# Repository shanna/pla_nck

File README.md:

# PLA_NCK

A low profile split keyboard I built using Gateron KS-33 low profile switches.

## Story

I had assembled a Ferris Sweep previously but I hated the Kailh Low Profile Choc Switches but but wanted something low profile.
Sincve I couldn't find anything at the time I decided to learn KiCad and Fusion360 to create my own design.

I've called it the PLA_NCK because my original intention was to create a split [ZSA Planck EZ](https://blog.zsa.io/2307-goodbye-planck-ez/) (discontinued) since it has probably been my favourite layout to date. I justed wanted a split, bluetooth and low profile version with Gateron KS-33 switches after using the [NuPhy Air60](https://nuphy.com/collections/keyboards/products/air60) with [Daisy](https://nuphy.com/collections/switches/products/nuphy-daisy-l48-switches) Gateron colaboration switches.
I couldn't quite fit the controller under the keys while keeping it low so I gave up and added the nice view as well for this version so my homage to the original Planck is a bit shit. 
I might attempt it again with without a pre-made controller when my KiCad skills improve so I can ditch the display and make it closer to the split plank low profile vision I started with.

## BOM

The AliExpress stuff will be hit and miss.

* NuPhy [Daisy](https://nuphy.com/collections/switches/products/nuphy-daisy-l48-switches) switches.
* NuPhy [COAST Twilight nSA Dye-sub PBT Keycaps](https://nuphy.com/collections/keycaps/products/twilight-nsa-dye-sub-pbt-keycaps)
* GATERON KS-27 or KS-33 [Low Profile switch Hot-swap PCB 2.0 Socket](https://www.aliexpress.com/item/1005004128409069.html) these were hard to find.
* PCB and Plate [JLCPCB](https://jlcpcb.com) was much cheaper than PCBWay when I got a quote for the exported gerbers. The quaility was fine.
* 4xM2 4mm screws.
* 8xM2 12-14mm screws.
* 12 x [M2 OD3.5mm 3mm](https://www.aliexpress.com/item/1005003582355741.html) brass hot melt insert nuts.
* 3D printer for the case, cover and optional nice view guard.

## Build

Everything you need is included in this repo I think.

1. You need to order both the plate and PCB as the GATERON KS-33 keys are only 3 pin and don't have the plastic alignment tabs so can only be used hot-swap with this design.
2. The nice view guard is in case you are worried about shorting your nice view on the battery case material.
3. I 3D printed the cover without a top and bottom layer using 60% infilled 3D honeycomb pattern. I paused the print at layer 78 to change my matte black PLA out for matte grey. I've included the bambu studio files if you happen to own a Bambu Labs printer or can use the configuration.

### CAD - V1 3D Printed Case 

Version 1 I tried to add mass by printing the case with 60% infill in PLA and hoped it would improve the sound. It was better than nothing but a bit too loud for the office.

### CAD - V2 3D Printed Case

Version 2 I've simplified the PLA case and printed a mount in TPU that sits between the PCB and plate and bolts directly to the case. Keyboard switch sounds is subjective (some blue use MX blues) but this removed a lot of the high frequency plastic "ping" I wasn't happy with. There is still room for improvement if you have any ideas. I've been experimenting with different foams and TPU inserts in the case to remove more of the high frequencies because I want more "thock" and less "clack".

## Firmware

I'm running ZMK on my nice!nano's. The config/ directory contains all the ZMK config you need to match the pin-out and diode direction along with my current key map (which sucks but is a starting point).

The makefile expects nix to be installed and runs 'act' the local github actions runner to test the ZMK github actions. It has nowhere to write artifacts out to but is handy for checking your configuration files are valid before uploading them to github.

## Issues

Tolerances are tight, too tight in places, depending on the PCB manufacturer and 3D printer setup and material you print in. I used PLA but I still struggled with shrinkage so tried to hide it with some shadow lines.

* The switch footprint is slightly too tight and can locks on to the switch housing making it hard to hot-swap switches.
* The plate was a tight fit, again making the switches hard to hot-swap.
* My attempt at an injection molding style shadow lines could be improved. They just look like gaps between the PCB and case because I made them so deep.
* It would be cool if the USB and power switch gap was more exact and the PCB lined up with the side of the 3D printed case a bit better.

## Gallery

### V1

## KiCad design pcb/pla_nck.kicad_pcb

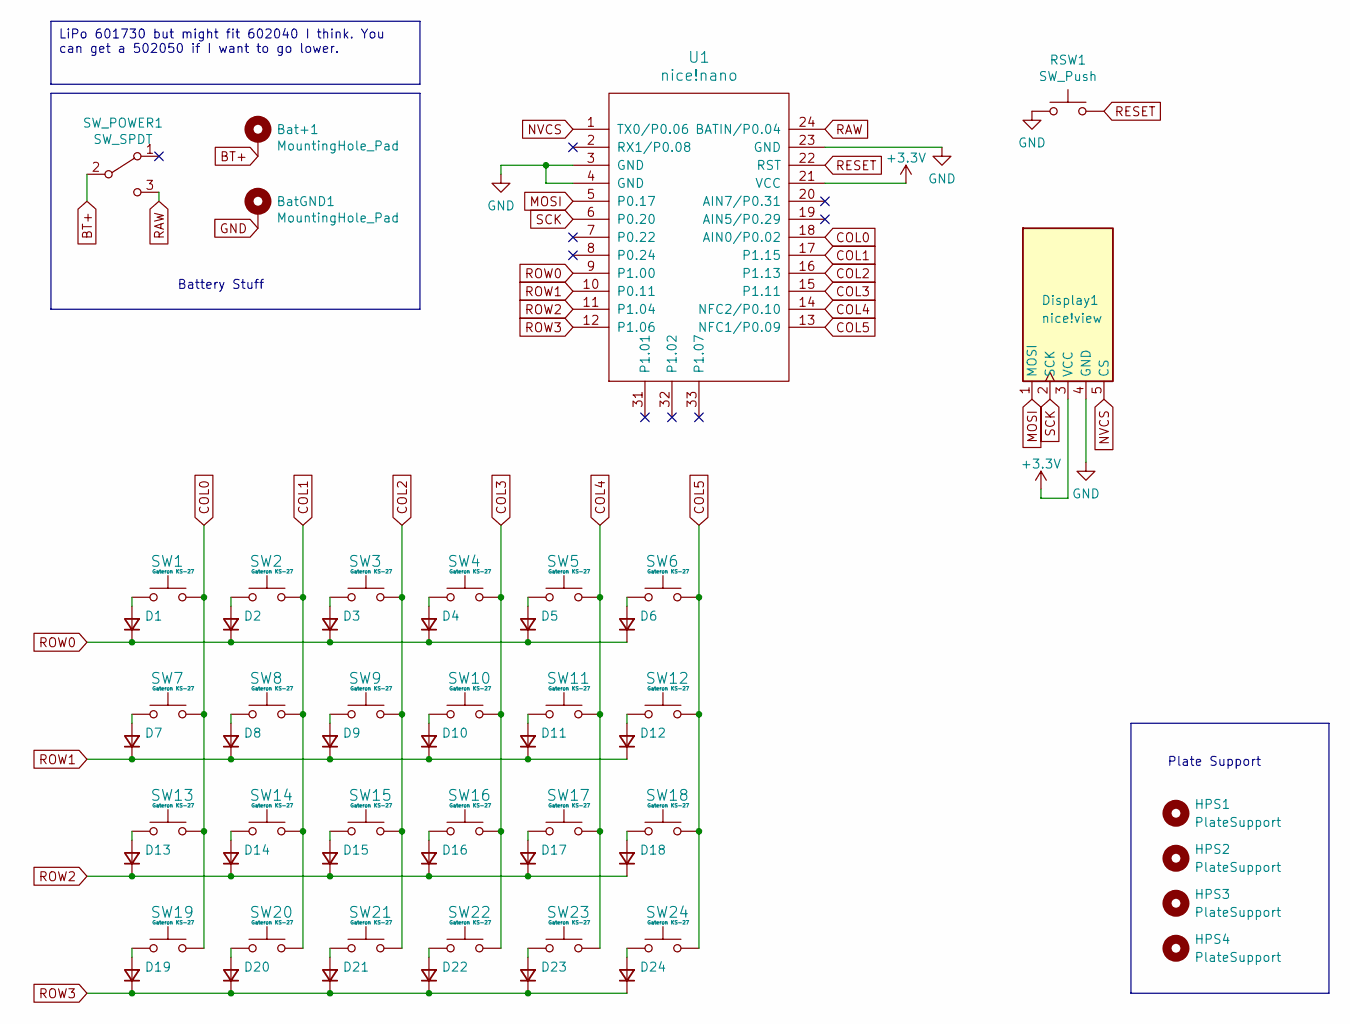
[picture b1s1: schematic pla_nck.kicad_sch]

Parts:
Bat+1: MountingHole_Pad; 1pin_battery_v2
BatGND1: MountingHole_Pad; 1pin_battery_v2
D1, D2, D3, D4, D5, D6, D7, D8, D9, D10, D11, D12, D13, D14, D15, D16, D17, D18, D19, D20, D21, D22, D23, D24: diode; D_SOD-123
Display1: nice!view; nice_view
HPS1, HPS2, HPS3, HPS4: PlateSupport; MountingHole_2.2mm_M2
RSW1: SW_Push; SW_RESET
SW1, SW2, SW3, SW4, SW5, SW6, SW7, SW8, SW9, SW10, SW11, SW12, SW13, SW14, SW15, SW16, SW17, SW18, SW19, SW20, SW21, SW22, SW23, SW24: Gateron KS-27; SW_Gateron_LO_PRO_1.00u_HOTSWAP_NO_LED_PCB
SW_POWER1: SW_SPDT; smt-slider-switch
U1: nice!nano; nice_nano

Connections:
+3V3: Display1.3 (VCC), U1.21 (VCC)
BT+: Bat+1.1, SW_POWER1.2 (B)
COL0: SW1.2, SW7.2, SW13.2, SW19.2, U1.18 (AIN0/P0.02)
COL1: SW2.2, SW8.2, SW14.2, SW20.2, U1.17 (P1.15)
COL2: SW3.2, SW9.2, SW15.2, SW21.2, U1.16 (P1.13)
COL3: SW4.2, SW10.2, SW16.2, SW22.2, U1.15 (P1.11)
COL4: SW5.2, SW11.2, SW17.2, SW23.2, U1.14 (NFC2/P0.10)
COL5: SW6.2, SW12.2, SW18.2, SW24.2, U1.13 (NFC1/P0.09)
GND: BatGND1.1, Display1.4 (GND), RSW1.1, U1.3 (GND), U1.4 (GND), U1.23 (GND)
MOSI: Display1.1 (MOSI), U1.5 (P0.17)
NVCS: Display1.5 (CS), U1.1 (TX0/P0.06)
unnamed: D1.2 (A), SW1.1
unnamed: D2.2 (A), SW2.1
unnamed: D3.2 (A), SW3.1
unnamed: D4.2 (A), SW4.1
unnamed: D5.2 (A), SW5.1
unnamed: D6.2 (A), SW6.1
unnamed: D7.2 (A), SW7.1
unnamed: D8.2 (A), SW8.1
unnamed: D9.2 (A), SW9.1
unnamed: D10.2 (A), SW10.1
unnamed: D11.2 (A), SW11.1
unnamed: D12.2 (A), SW12.1
unnamed: D13.2 (A), SW13.1
unnamed: D14.2 (A), SW14.1
unnamed: D15.2 (A), SW15.1
unnamed: D16.2 (A), SW16.1
unnamed: D17.2 (A), SW17.1
unnamed: D18.2 (A), SW18.1
unnamed: D19.2 (A), SW19.1
unnamed: D20.2 (A), SW20.1
unnamed: D21.2 (A), SW21.1
unnamed: D22.2 (A), SW22.1
unnamed: D23.2 (A), SW23.1
unnamed: D24.2 (A), SW24.1
RAW: SW_POWER1.3 (C), U1.24 (BATIN/P0.04)
RESET: RSW1.2, U1.22 (RST)
ROW0: D1.1 (K), D2.1 (K), D3.1 (K), D4.1 (K), D5.1 (K), D6.1 (K), U1.9 (P1.00)
ROW1: D7.1 (K), D8.1 (K), D9.1 (K), D10.1 (K), D11.1 (K), D12.1 (K), U1.10 (P0.11)
ROW2: D13.1 (K), D14.1 (K), D15.1 (K), D16.1 (K), D17.1 (K), D18.1 (K), U1.11 (P1.04)
ROW3: D19.1 (K), D20.1 (K), D21.1 (K), D22.1 (K), D23.1 (K), D24.1 (K), U1.12 (P1.06)
SCK: Display1.2 (SCK), U1.6 (P0.20)

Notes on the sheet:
LiPo 601730 but might fit 602040 I think. You can get a 502050 if I want to go lower.
Battery Stuff
Plate Support

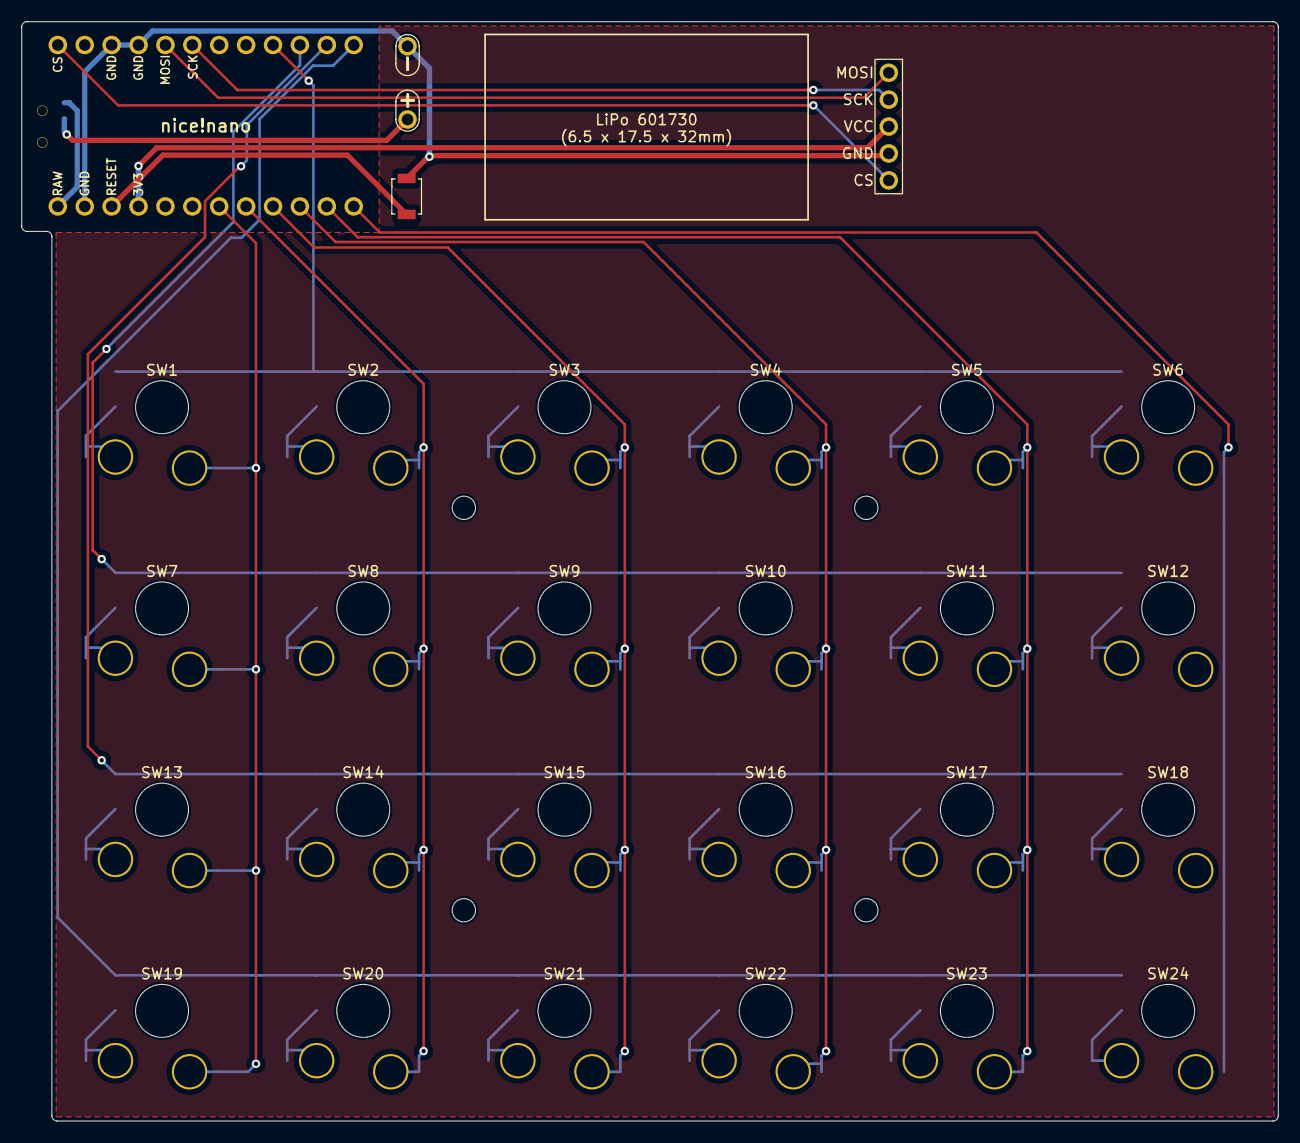
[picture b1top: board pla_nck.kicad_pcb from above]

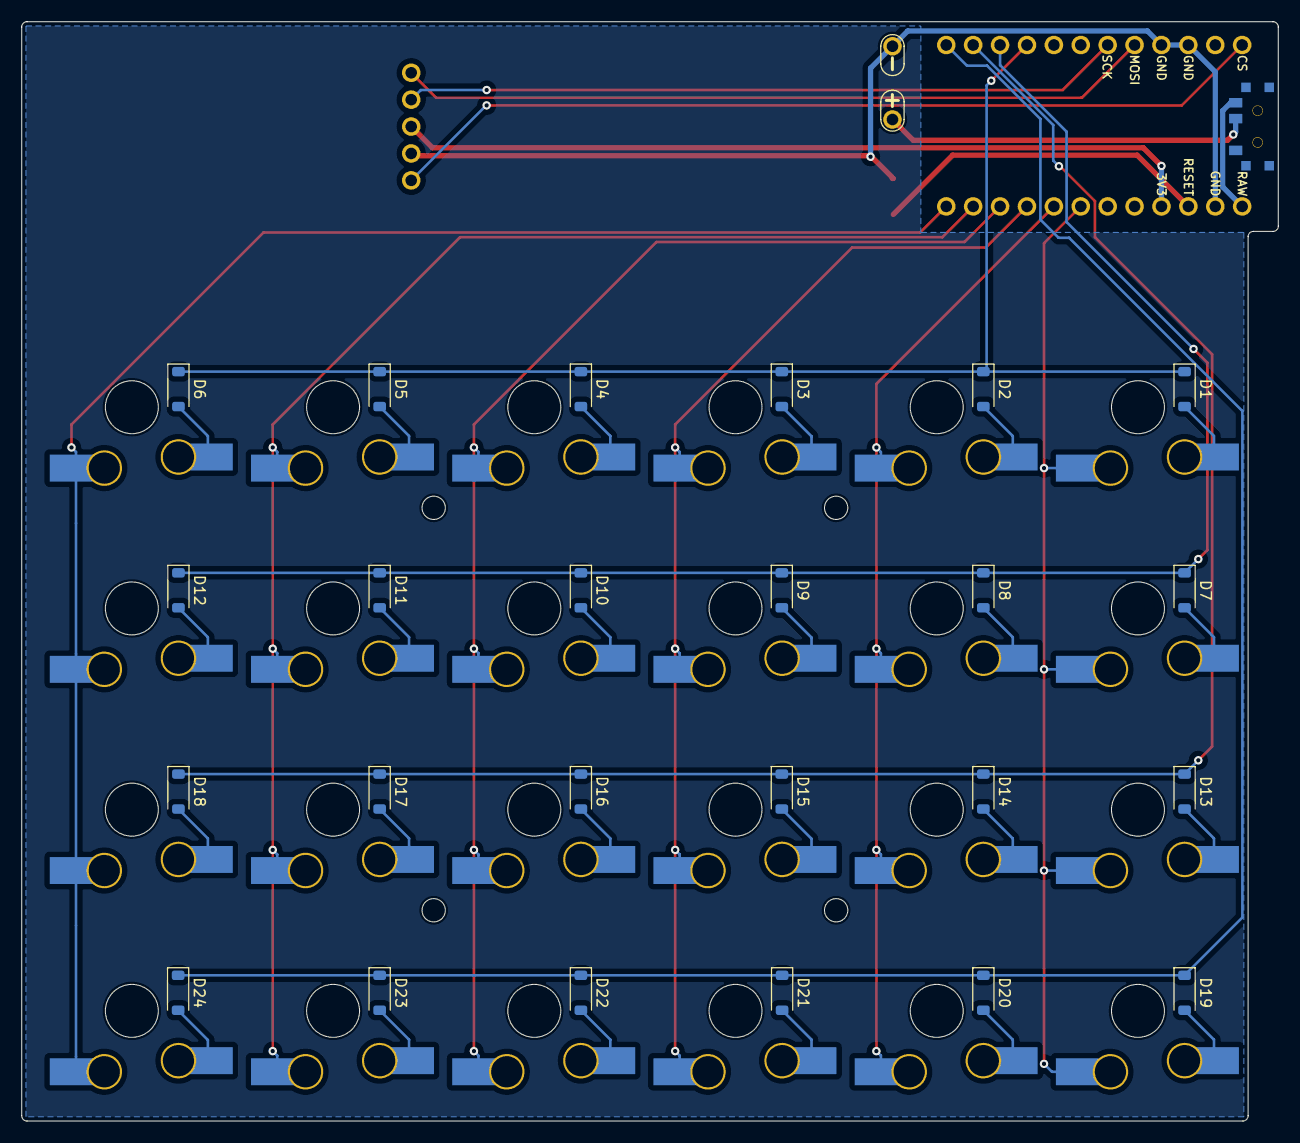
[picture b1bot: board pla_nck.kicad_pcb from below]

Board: 2 copper layers, 118.7 x 103.8 mm, 58 parts (26 on the bottom side), 42 nets.

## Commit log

2023-08-08 Initial User Config.
2023-08-08 PLA-NCK.
2023-08-08 Column order.
2023-08-08 Display.
2023-08-09 Displays.
2023-08-09 Disable vertical status screen.
2023-08-13 Add layers.
2023-08-14 Start adding macros. Move keymap to match my other plank.
2023-08-14 Typo.
2023-08-14 Bootloader and reset.
2023-08-15 Build details and CAD.
2023-08-15 Add firmware section to README.
2023-08-15 Add build issues to the README.
2023-08-16 OD was wrong on the brass inserts.
2023-08-25 Case version 2.
2023-08-25 Note I've only changed the case CAD.
2023-09-01 Gaming.
    Starfield shipped and I need a space key on my left hand to jump
    with.
2024-04-01 Add &mt meh to space keys.
2024-04-01 Move MEH to macro.
2024-04-01 Is HYPER is better or worse than MEH in windows?
2024-04-01 Space needs to be space.
    1. I can't handle the lag of MEH or HYPER on space.
    2. Windows has hijacked HYPER for windows bullshit. HYPER+L is
    linkedin. WTF.
2024-04-01 Left &mt behind when removing mod+tap from space.
2024-04-01 C macro failures?
    The build failures are gibberish and I can't get this to compile
    locally.
2024-04-04 keymap - Switch LGUI and LALT.
